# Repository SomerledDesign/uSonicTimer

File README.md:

# uSonicTimer

Firmware for a timer and heater controller I added to a cheap ultrasonic cleaner. It runs on an
**ESP8266 (ESP-12E module)**. A **Nokia 5110 (PCD8544, 84x48) LCD** shows a menu that you drive with a
**rotary encoder and its push button**. A **DS18B20 1-Wire temperature sensor** measures the bowl
temperature. Two outputs drive **solid-state relays** that switch the 110 VAC bowl **heater** and the
ultrasonic **cleaner**. The set temperature, timer preset, display unit (°F/°C), LCD contrast and
backlight brightness are saved in (emulated) EEPROM, so they survive a power cycle.

The menu approach comes from the [educ8s.tv](https://www.youtube.com/@Educ8s)
[menu tutorial](https://youtu.be/ak5TsUFhyf8?si=9JEMm8WbRyF4dVVC).

> Status: in active development (v0.6.1, PCB Rev D).

## What it does

1. On power-up it loads the settings from EEPROM. If a value is unset or out of range it uses a
   default: 72 °F, 10 min, °F, contrast 52 (raw 128), backlight level 10. It then initialises the
   LCD, the DS18B20, the encoder and the button.
2. It shows the main menu. You pick an item and a tap (short press) opens it; a long press toggles the backlight.
3. **Start** runs the cleaner for the set time and regulates the heater (the control logic always
   works in °F, with tenths; the screens show whole degrees in the chosen unit):
   - **Heating:** below set − 10 °F the **heater is ON**, the **cleaner is OFF** and the countdown
     **holds**. The screen shows the bowl temperature in big digits and "Heating to 120°F"; the
     rule under the digits fills as the bowl warms from where heating started to set − 8 °F.
   - **Cleaning:** at set − 8 °F or above (2 °F hysteresis) the **heater is OFF**, the **cleaner is
     ON** and the countdown runs. The screen shows the time left as big `MM:SS` with a blinking
     colon, the rule under it fills with the run's progress, and "Now 118 Set 120°F" underneath.
     If the bowl drops below set − 10 °F the heater comes back on and the countdown holds again.
     Only cleaning time counts towards the run.
   - **No sensor:** heater locked off, cleaner on, the countdown runs; the time screen shows
     "NO SENSOR" instead of the temperatures.
   - When the time is up both outputs switch off and a big **DONE** stays on screen until you turn
     or press; then the menu returns. A long press during the run aborts it (both outputs off).

## Menu tree

In the menus, rotating the encoder moves the reverse-video highlight (lists show 4 rows under the
title bar and scroll; small arrows mark more items). On the main menu a **short press** (tap) on
**Start** starts the timer and a tap on **Settings...** opens the Settings list; a **long press**
(> 1 s) on either toggles the LCD backlight between off and the level set in **Set backlight**.
In the Settings list a tap or a long press opens the highlighted item (**Exit** returns to the
main menu). The backlight is on at power-up.
Its state is kept while you are in a page, because presses inside the pages move the cursor
or confirm instead. After 5 minutes without input in the menu the backlight dims to about 20 %; the
first turn or press then only wakes it. Every button press is handled exactly once, so a press never
carries over into the next page.

**Encoder test:** hold the button while powering up (or pressing reset) to get a test screen with the
live A/B levels, the detent count and how often each input has changed; long press returns to the
menu. Both edge counts should rise together while turning. `ENCODER_STEPS_PER_DETENT` in
`src/main.cpp` is 2 for an encoder whose detents rest at both 00 and 11, 4 for one that always rests
at the same state.

The backlight also shows the status (it swings between the set brightness and about 30 % of it, so
the screen stays readable):

- **Steady**: normal operation (menu, cleaning).
- **Flashing** (1 Hz): heating up.
- **Pulsing** (slow): the timer has finished; stops at the next turn or press.
- **Double-blink** every 2 s: no temperature sensor during a run (heater locked off, cleaner runs).

Pulsing and double-blink also show when the backlight has been toggled off or set to level 0 (then
at level 5); heating and cleaning then stay dark.

```
Main menu "uSonicTimer"      (shows the set temperature and time underneath)
├── Start             heating screen (big temperature) / timer screen (big MM:SS) / DONE, as above
│                     long press = abort (both outputs off)
└── Settings...
    ├── Set temp      "ddd°F" (3 digits) or "dd°C" (2 digits), cursor digit in reverse video
    │                 rotate = change digit (0–9, wraps); press = next digit ("Press = next"),
    │                 press on the last digit = save and return ("Press = save");
    │                 long press = save from any digit (clamped 60–180 °F / 16–82 °C, stored in °F)
    ├── Set time      "<n> min"; rotate = preset 3, 8, 10, 15, 20, 30, 60 min (wraps)
    │                 press = save and return
    ├── Set units     "°F Fahrenheit" / "°C Celsius"; rotate = toggle, press = save and return
    ├── Set backlight "Off" / "Level 1"…"Level 10" with a bar; rotate = level (previewed live)
    │                 press = save, switch the backlight on and return
    ├── Set contrast  20–100 with a bar (mapped onto the usable raw 80–200); clockwise = higher,
    │                 accelerated (detents < 40 ms apart = 5 steps, < 90 ms = 2, else 1),
    │                 applied live; press = save and return
    └── Exit          back to the main menu
```

Settings are saved to EEPROM when you leave their page: set temperature `0x00` (°F), time `0x08`,
contrast `0x10` (raw 80–200, so the 0.5.0 value carries over), backlight level `0x18`, units `0x20`
(0 = °F, 1 = °C) and a layout id `0x28` (0x60) that marks EEPROM written by 0.6.0 or later. Every
value is range-checked on load; a backlight level of 0 is only accepted together with that id.

## Hardware (PCB rev 1d) pin map

The KiCad design files for this board are in [`hardware/uSonicTimer_1d/`](hardware/uSonicTimer_1d/).

| Signal | Arduino pin | ESP8266 GPIO | ESP-12E pin | Notes |
|---|---|---|---|---|
| LCD SCLK | D5 | GPIO14 | 5 | software SPI clock |
| LCD DIN | D7 | GPIO13 | 7 | software SPI data |
| LCD D/C | D10 | GPIO1 (TX) | 22 | shared with UART TX |
| LCD CS | D4 | GPIO2 | 17 | 10K pull-up |
| LCD RST | – | – | – | not connected (`U8X8_PIN_NONE`) |
| LCD backlight | D8 | GPIO15 | 16 | via Q1, 10K pull-down |
| Encoder CLK (A) | D0 | GPIO16 | 4 | 4K7 pull-up (R9), polled (no interrupt on GPIO16) |
| Encoder DT (B) | D6 | GPIO12 | 6 | 4K7 pull-up (R10), polled |
| Encoder SW | D9 | GPIO3 (RX) | 21 | shared with UART RX |
| Heater SSR | D2 | GPIO4 | 19 | HIGH = ON |
| Cleaner SSR | D1 | GPIO5 | 20 | HIGH = ON |
| DS18B20 1-Wire | D3 | GPIO0 | 18 | 4K7 pull-up; also ~PROGRAM strap |

On rev 1d, NPN transistors switch the heater and cleaner SSRs low-side. The logic is the same as
before: GPIO HIGH = ON.

The programming header is a set of 5 pogo pads: 1 GND, 2 RTS, 3 TX, 4 RX, 5 DTR. RTS and DTR
drive the auto-reset/boot circuit (Q2/Q3).

Because the UART pins are also used for the LCD D/C line and the encoder switch, serial output
from the `debug` build shares those lines with the hardware.

## Building and flashing (PlatformIO)

The project uses the `espressif8266` platform, board `esp12e` and the Arduino framework. It needs
these libraries, which PlatformIO fetches automatically from `platformio.ini`:
`olikraus/U8g2`, `lennarthennigs/ESP Rotary`, `lennarthennigs/Button2`, `paulstoffregen/OneWire`
and `milesburton/DallasTemperature`. `EEPROM` and `Ticker` come with the ESP8266 core.

```sh
pio run -e release                  # build the release firmware
pio run -e release -t upload        # flash it over the programming header
pio device monitor -b 115200        # serial monitor (debug output)
```

- `release` is the default environment (`default_envs = release`); it builds without the debug
  output.
- `debug` (`pio run -e debug`) adds `-Og -ggdb -g3 -D DEBUG -D WITH_GDB`. It enables the
  serial `debug()`/`debugln()` output at 115200 baud.
- `platformio.ini` puts `build_dir` and `libdeps_dir` under
  `$HOME/Library/Caches/PlatformIO/uSonicTimer/`, which keeps build output out of Dropbox. On a
  non-macOS machine, change these paths or remove them to use the default `.pio/` folder.

### Uploading over the pogo pins (FTDI 3.3 V cable, no DTR)

The programming cable (FTDI TTL-232R 3.3 V with LED) has no DTR line, so it can't put the ESP8266
into flash mode by itself. Do it by hand:

1. Short the sensor connector's data / 1-Wire line (GPIO0) to ground.
2. Turn the uSonicTimer on, or off and back on, so it boots into the bootloader. Power it from a
   5 V supply rather than mains, so no mains voltage is exposed on the bench.
3. Place the pogo pins on the programming pads: GND (black), RTS (green), the cable's TXD (orange) to
   the board's RX, and the cable's RXD (yellow) to the board's TX. Leave the cable's 5 V (red) and CTS (brown) unconnected.
4. Upload from VS Code (PlatformIO Upload). The upload speed is 115200.

Remove the GPIO0 short afterwards, then power-cycle the board to run the new firmware.

## Versioning

Firmware versions are a semantic version plus a build number, shown as **`0.6.2 (74)`** (current).

- Bump PATCH for fixes and MINOR for features; 1.0.0 is the first version installed and in service.
- The build number goes up by 1 for every build flashed for testing and never resets.
- `FW_VERSION`, `FW_BUILD` and `HW_REV` at the top of `src/main.cpp` set it. The startup screen
  shows `uSonicTimer` / `v0.6.2 (74)` / `PCB Rev D` for 1.5 s at power-up. Releases are tagged
  `vMAJOR.MINOR.PATCH` in git.

History:

- **0.6.2 (74)**: new button mapping. Main menu: tap on **Start** starts the timer, tap on
  **Settings...** opens the Settings list, long press on either toggles the backlight. Settings
  list: tap or long press opens the highlighted item.
- 0.6.1 (73): new big-digit font: blocky, squared-off 7-segment-style characters (4–5 px
  strokes, no diagonals, stepped slashed zero, colon of two 4x4 blocks) drawn from box lists in
  `include/bigfont.h`, closer to the reference clock than the scaled 5x7 font. Encoder
  acceleration in Set contrast (5 / 2 / 1 steps per detent for detents
  < 40 ms / < 90 ms / slower apart). A press saves in every settings page ("Press = save"); in Set
  temp a press moves to the next digit and saves on the last one, long press still saves anywhere.
  Detents still queued when a page closes no longer move the menu highlight.
- 0.6.0 (72): big-digit run screens in the style of a Nokia 5110 clock (Adafruit 5x7 digits
  scaled to 15x28 px, a rule that doubles as a progress bar, one line of small text): heating
  screen with the bowl temperature, timer screen with blinking colon, DONE screen. The countdown
  holds while heating (heater below set − 10 °F, cleaning resumes at set − 8 °F). Main menu is now
  Start / Settings...; Settings has Set temp, Set time, Set units (°F/°C, new), Set backlight
  (0 = off, new), Set contrast (shown as 20–100) and Exit, with title bars.
- 0.5.0 (71), `2d4bacc`: version defines, startup screen, versioning notes.
- Build 70, `a255348`: polled quadrature decoder (replaces ESPRotary) and the encoder test screen.
- Build 69, `44c0249`: backlight as status indicator and the Backlight brightness menu (`90cbc71`).

## Setup and usage

1. Wire the board as in the pin map, or use the rev 1d PCB. Put the DS18B20 on the bowl and
   connect the heater and cleaner through the SSRs.
2. Build and flash as above, then power up. The main menu appears.
3. Tap **Settings...** to open it and use **Set temp** to choose the target bowl temperature, **Set time**
   to choose the run time, **Set units** for °F or °C, and **Set backlight** / **Set contrast** for
   the LCD if needed. Each setting is saved when you leave its page.
4. Highlight **Start** and tap (short press). The display shows the bowl temperature while it heats, then
   the time left while it cleans; the heater and cleaner are controlled automatically.
5. Long-press at any time to stop. Both outputs switch off. When the time is up, DONE shows until
   you turn or press.

## Repository layout

- `src/main.cpp`: the firmware (setup, menus, pages, run control, EEPROM, backlight).
- `src/screens.cpp`, `include/screens.h`: drawing for the run screens, menus and settings pages.
- `include/ust_logic.h`: run-control hysteresis, °F/°C, contrast and progress helpers (no Arduino
  dependencies).
- `include/bigfont.h`: the big-digit font (blocky 15x28 characters as box lists, slashed zero).
- `tools/host/`: host-side test of `ust_logic.h` and a screen preview that runs the real drawing
  code against the U8g2 C library on a PC (`tools/host/build.sh`, writes PNGs to
  `tools/host/out/`).
- `src/sketch.md`: design notes and the original specification.
- `include/`: also the old splash/footer glyph bitmaps.
- `handoff.md`: latest status and decisions.
- `hardware/uSonicTimer_1d/`: KiCad project for the rev 1d controller board (schematic, PCB,
  project symbol/footprint libraries, Gerbers, interactive BOM and renders).
- `extras/` (git-ignored): local reference material. This includes third-party menu/encoder demo
  code, links to the KiCad hardware projects and links to the datasheets, which are archived
  centrally.

## License

uSonicTimer uses two licences, one for the code and one for the hardware:

- **Firmware and code** (`src/`, `include/`, `platformio.ini` and the rest of the software) are
  under the GNU General Public License, version 3 or later. See [`LICENSE`](LICENSE).
  SPDX-License-Identifier: GPL-3.0-or-later
- **Hardware design files** (everything under [`hardware/`](hardware/): the KiCad schematic,
  PCB, libraries and related fabrication files for the controller board, and the same files
  wherever else they are published for this project) are under the CERN Open Hardware Licence
  Version 2, Strongly Reciprocal. See [`LICENSE-HARDWARE`](LICENSE-HARDWARE).
  SPDX-License-Identifier: CERN-OHL-S-2.0

Both licences come with no warranty. This controller switches 110 VAC mains through solid-state
relays; build and use it at your own risk.

Copyright © 2024 Somerled Design, LLC.

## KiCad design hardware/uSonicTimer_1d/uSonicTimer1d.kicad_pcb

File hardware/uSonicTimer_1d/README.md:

# uSonicTimer controller board, rev 1d

KiCad 10 project for the uSonicTimer controller PCB (schematic rev D). The firmware
pin map in the top-level [`README`](../../README.md) matches this board.

| Path | Contents |
|---|---|
| `uSonicTimer1d.kicad_pro` | KiCad project (open this) |
| `uSonicTimer1d.kicad_sch` | Schematic |
| `uSonicTimer1d.kicad_pcb` | PCB layout |
| `uSonicTimer1d.kicad_dru` | Custom design rules |
| `uSonicTimer1d.kicad_sym`, `sym-lib-table` | Project symbol library |
| `uSonicTimer1d.pretty/`, `fp-lib-table` | Project footprint library |
| `3dmodels/` | Project 3D models folder (currently only a README: sources, licences and excluded models) |
| `Gerber/` | Fabrication outputs: Gerbers, drill files, job file and `uSonicTimer1d_revD_gerbers.zip` for ordering |
| `bom/ibom.html` | Interactive BOM (open in a browser) |
| `Renders/` | Top and bottom board renders |
| `[TODO]/` | Changes planned for the next board revision |

The library tables use `${KIPRJMOD}`, so the project opens from any location. Every
symbol and footprint is in the project libraries. Every 3D model comes from the stock
KiCad 10 3D library, so nothing is needed outside this folder and a standard KiCad 10
install. The encoder (ENC1) and the screw terminal (J1) have no 3D body: their
third-party models can't be redistributed. Sources and licences are listed in
[`3dmodels/README.md`](3dmodels/README.md).

Licensed under the CERN Open Hardware Licence Version 2, Strongly Reciprocal. See
[`LICENSE-HARDWARE`](../../LICENSE-HARDWARE).
SPDX-License-Identifier: CERN-OHL-S-2.0

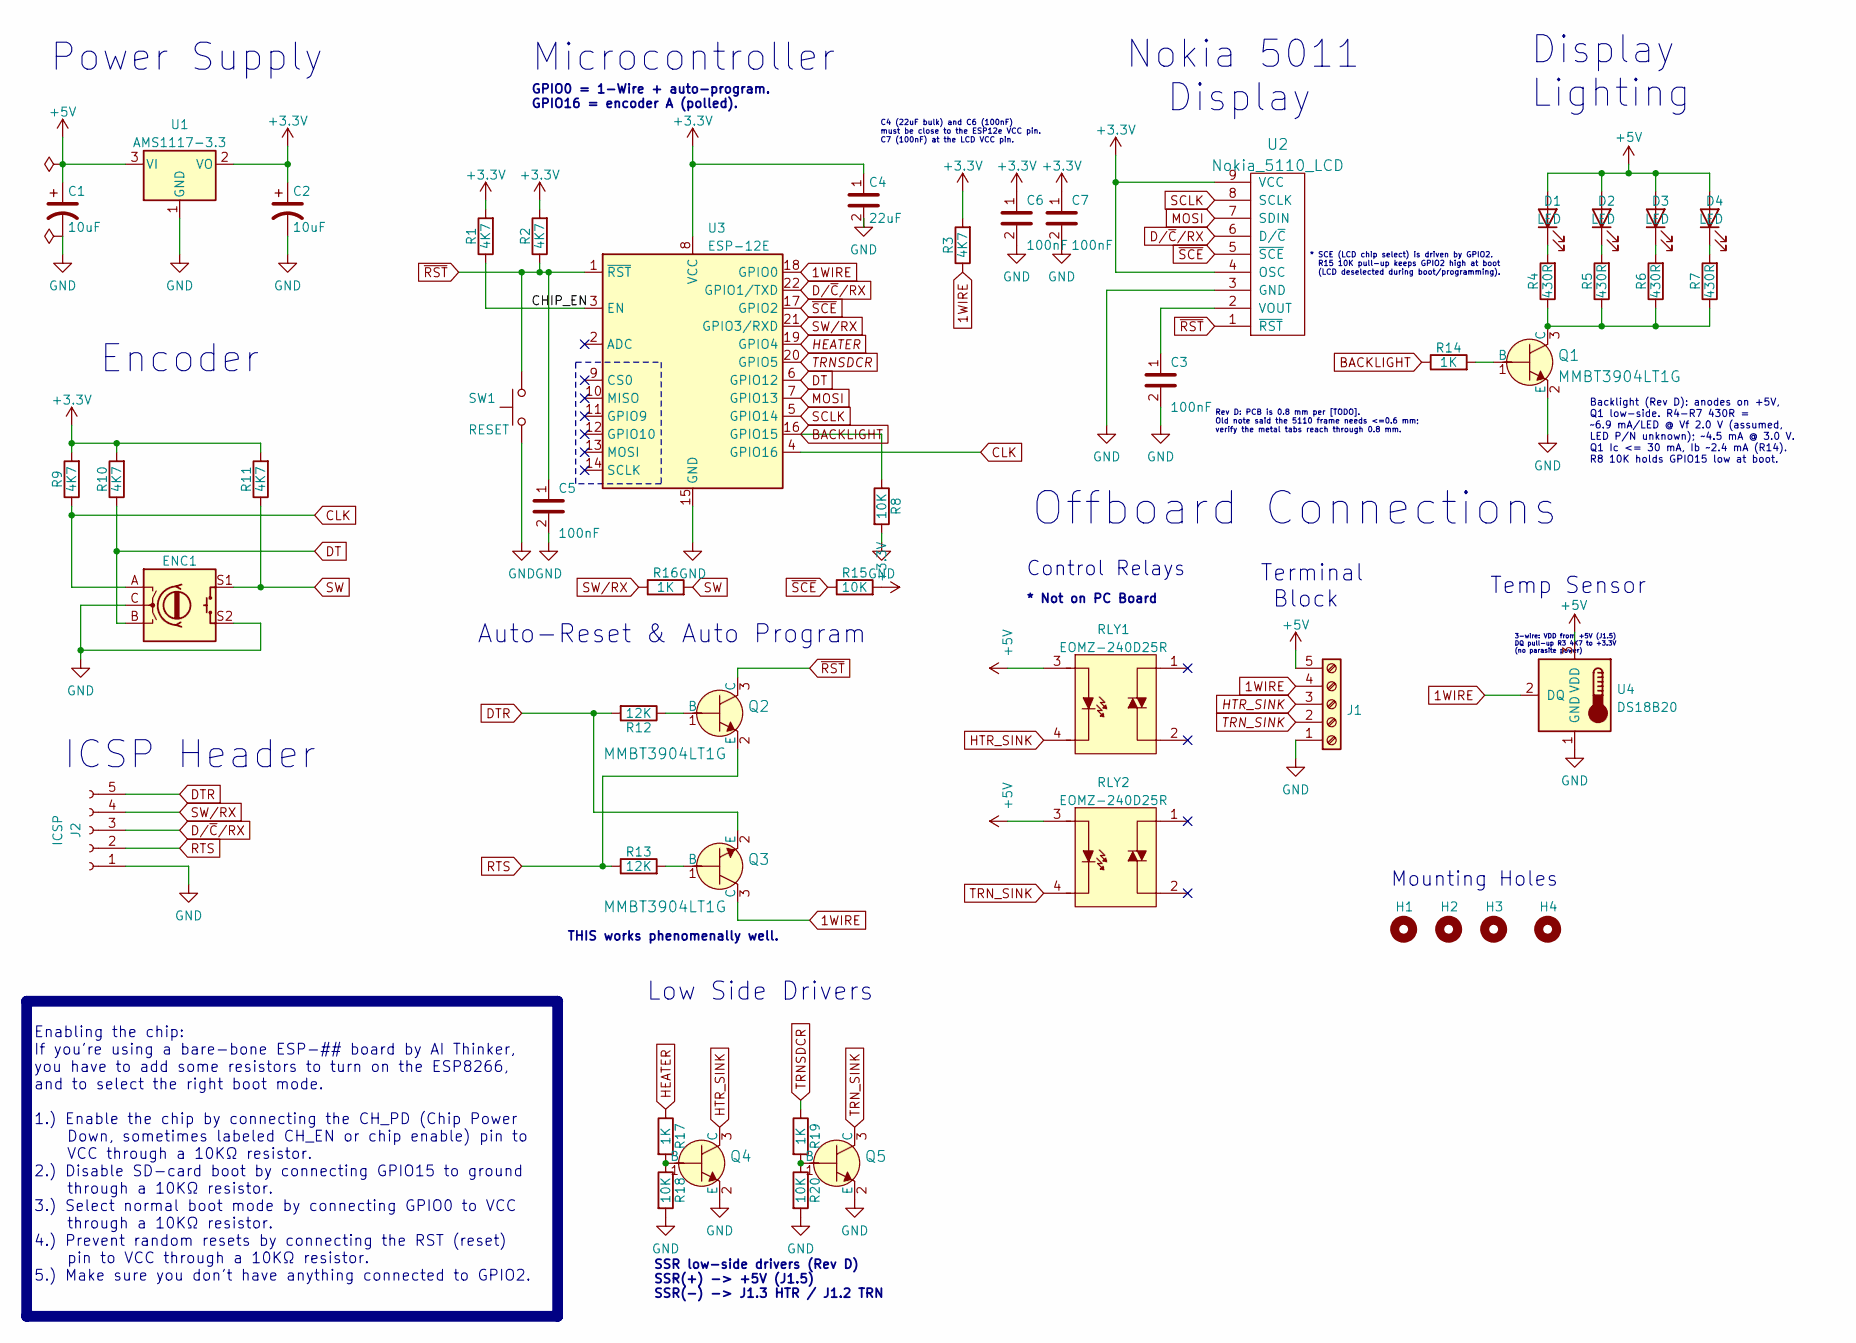
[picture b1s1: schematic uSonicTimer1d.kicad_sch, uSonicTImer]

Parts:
C1, C2: 10uF; CP_Elec_4x5.4; MPN UWT1C100MCL1GB; Digikey PN 493-2173-1-ND
C3, C5, C6, C7: 100nF; C_0805_2012Metric; MPN 08055C104KAT4A; Digikey PN 478-10836-1-ND
C4: 22uF; C_1206_3216Metric
D1, D3: LED; LED_0805_2012Metric
D2: LED; LED_0805_2012Metric_SilkTrim_D2
D4: LED; LED_0805_2012Metric_SilkTrim_D4
ENC1: RotaryEncoder_Switch; RotaryEncoder_Alps_EC11E-Switch_Vertical_H20mm
H1, H2, H3, H4: MountingHole; MountingHole_2.1mm
J1: Screw_Terminal_01x05; ScrewContact_ALLELEC_2,5_5-G-5,00_1x05_P5.00mm_Horizontal_c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
J2: ICSP; ICSP_5_POGO
Q1, Q2, Q3, Q4, Q5: MMBT3904LT1G; SOT-23-3; MPN MMBT3904LT1G; Digi-Key_PN MMBT3904LT1GOSCT-ND
R1, R2, R3, R9, R10, R11: 4K7; R_0805_2012Metric; MPN CRGCQ0805J4K7; Digikey PN A130138CT-ND
R4, R5, R6, R7: 430R; R_0805_2012Metric
R8, R15, R18, R20: 10K; R_0805_2012Metric; MPN CRGCQ0805J10K; Digikey PN A130140CT-ND
R12, R13: 12K; R_0805_2012Metric; MPN CRG0805F12K; Digikey PN A126337CT-ND
R14, R16, R17, R19: 1K; R_0805_2012Metric
RLY1, RLY2: EOMZ-240D25R; MPN EOMZ-240D25R; Digi-Key_PN SSR-240D25R
SW1: RESET; SW_Tactile_SPST_NO_Straight_CK_PTS636Sx25SMTRLFS
U1: AMS1117-3.3; SOT-223-3_TabPin2
U2: Nokia_5110_LCD; Nokia_5110-3310_LCD_uSonic1d
U3: ESP-12E
U4: DS18B20; TO-92_Inline

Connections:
1WIRE: J1.4, Q3.3 (C), R3.1, U3.18 (GPIO0), U4.2 (DQ)
+3.3V: C2.1, C4.1, C6.1, C7.1, R1.2, R2.2, R3.2, R9.2, R10.2, R11.2, R15.2, U1.2 (VO), U2.4 (OSC), U2.9 (VCC), U3.8 (VCC)
+5V: C1.1, D1.2 (A), D2.2 (A), D3.2 (A), D4.2 (A), J1.5, RLY1.3 (A), RLY2.3 (A), U1.3 (VI), U4.3 (VDD)
/CHIP_EN: R1.1, U3.3 (EN)
BACKLIGHT: R8.1, R14.1, U3.16 (GPIO15)
CLK: ENC1.A, R9.1, U3.4 (GPIO16)
DT: ENC1.B, R10.1, U3.6 (GPIO12)
DTR: J2.5, Q3.2 (E), R12.2
D/~C/RX: J2.3, U2.6 (D/~C), U3.22 (GPIO1/TXD)
GND: C1.2, C2.2, C3.2, C4.2, C5.2, C6.2, C7.2, ENC1.C, ENC1.S2, J1.1, J2.1, Q1.2 (E), Q4.2 (E), Q5.2 (E), R8.2, R18.2, R20.2, SW1.1, U1.1 (GND), U2.3 (GND), U3.15 (GND), U4.1 (GND)
HEATER: R17.1, U3.19 (GPIO4)
HTR_SINK: J1.3, Q4.3 (C), RLY1.4 (K)
MOSI: U2.7 (SDIN), U3.7 (GPIO13)
unnamed: D1.1 (K), R4.2
unnamed: D2.1 (K), R5.2
unnamed: D3.1 (K), R6.2
unnamed: D4.1 (K), R7.2
unnamed: Q1.1 (B), R14.2
unnamed: Q1.3 (C), R4.1, R5.1, R6.1, R7.1
unnamed: Q2.1 (B), R12.1
unnamed: Q3.1 (B), R13.2
unnamed: Q4.1 (B), R17.2, R18.1
unnamed: Q5.1 (B), R19.2, R20.1
unnamed: C3.1, U2.2 (VOUT)
RTS: J2.2, Q2.2 (E), R13.1
SCLK: U2.8 (SCLK), U3.5 (GPIO14)
SW: ENC1.S1, R11.1, R16.2
SW/RX: J2.4, R16.1, U3.21 (GPIO3/RXD)
TRNSDCR: R19.1, U3.20 (GPIO5)
TRN_SINK: J1.2, Q5.3 (C), RLY2.4 (K)
~RST: C5.1, Q2.3 (C), R2.1, SW1.2, U2.1 (~RST), U3.1 (~RST)
~SCE: R15.1, U2.5 (~SCE), U3.17 (GPIO2)

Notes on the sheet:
Auto-Reset & Auto Program
Terminal Block
SSR low-side drivers (Rev D) SSR(+) -> +5V (J1.5) SSR(-) -> J1.3 HTR / J1.2 TRN
Low Side Drivers
Control Relays
Mounting Holes
* SCE (LCD chip select) is driven by GPIO2. R15 10K pull-up keeps GPIO2 high at boot (LCD deselected during boot/programming).
Offboard Connections
Nokia 5011 Display
* Not on PC Board
GPIO0 = 1-Wire + auto-program. GPIO16 = encoder A (polled).
Microcontroller
Rev D: PCB is 0.8 mm per [TODO]. Old note said the 5110 frame needs <=0.6 mm; verify the metal tabs reach through 0.8 mm.
Display Lighting
ICSP Header
C4 (22uF bulk) and C6 (100nF) must be close to the ESP12e VCC pin. C7 (100nF) at the LCD VCC pin.
Temp Sensor
3-wire: VDD from +5V (J1.5) DQ pull-up R3 4K7 to +3.3V (no parasite power)
Power Supply
THIS works phenomenally well.
Encoder
Backlight (Rev D): anodes on +5V, Q1 low-side. R4-R7 430R = ~6.9 mA/LED @ Vf 2.0 V (assumed, LED P/N unknown); ~4.5 mA @ 3.0 V. Q1 Ic <= 30 mA, Ib ~2.4 mA (R14). R8 10K holds GPIO15 low at boot.
Enabling the chip: If you're using a bare-bone ESP-## board by AI Thinker, you have to add some resistors to turn on the ESP8266, and to select the right boot mode. 1.) Enable the chip by connecting the CH_PD (Chip Power Down, sometimes labeled CH_EN or chip enable) pin to VCC through a 10KΩ resist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

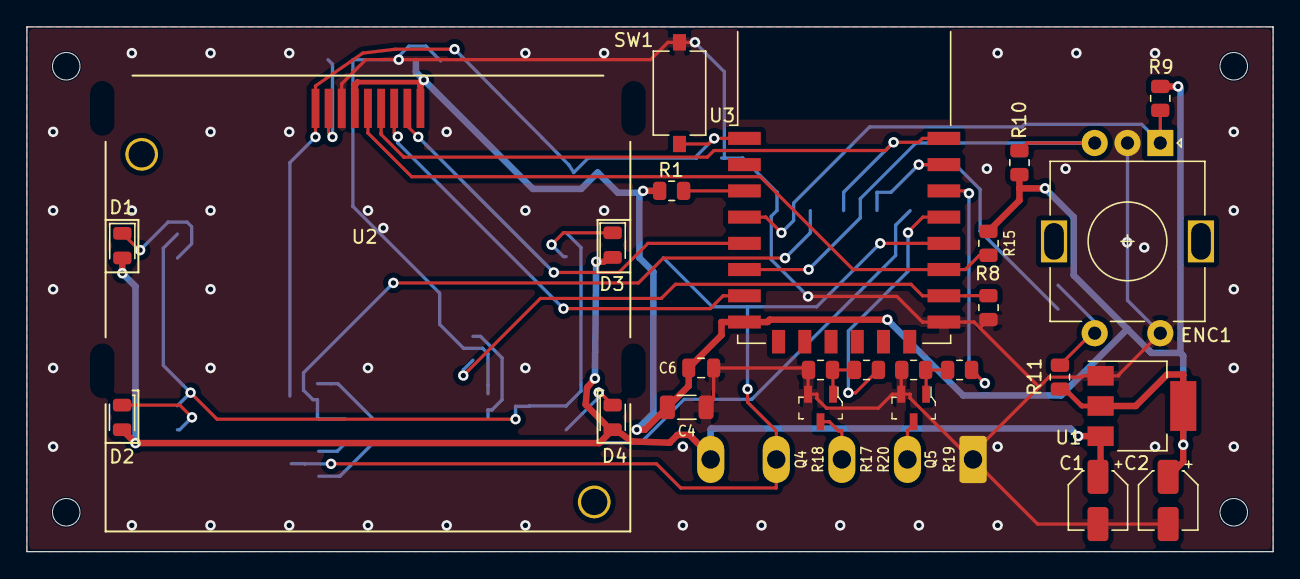
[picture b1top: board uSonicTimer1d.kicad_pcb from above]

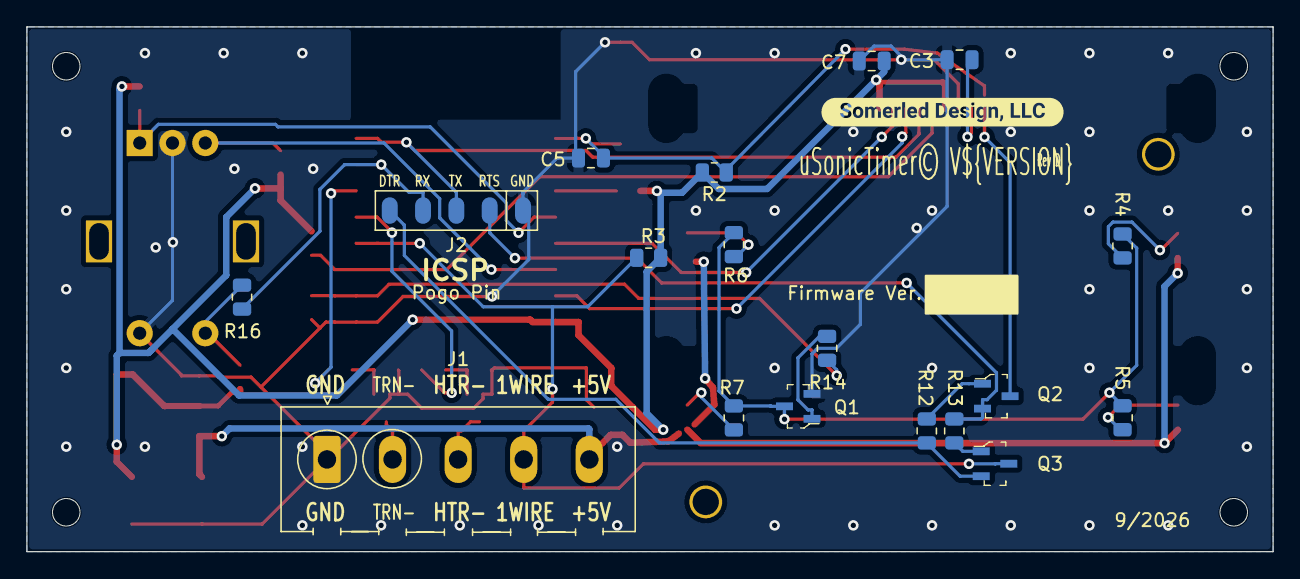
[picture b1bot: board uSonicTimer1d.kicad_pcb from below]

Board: 2 copper layers, 95.0 x 40.0 mm, 48 parts (19 on the bottom side), 32 nets.

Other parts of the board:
kibuzzard-63EC72D8: G***; kibuzzard-63EC72D8

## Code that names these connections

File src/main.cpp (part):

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/**
 *  Physical pins listed for comparison to pcb.
 *  in version 1b pcb 2/2023 the CS is connected to ground
 *  GPIO15 is used for
 *  PCB rev 1d (9/2026): LCD CS on GPIO2 (10K pull-up), backlight on GPIO15 (10K pull-down),
 *  1-Wire on GPIO0 (4K7 pull-up), encoder CLK on GPIO16. Heater/cleaner SSRs are now switched
 *  low-side by NPN transistors (GPIO HIGH = ON, same logic as before).
 *
 *
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 *   •   RST             1
 *
 *  --- Available  I/O ---
 *   •   GPIO0     D3   18
 *   •   GPIO1     D10  22  (TXD0) \
 *   •   GPIO3     D9   21  (RXD0)  |  If using as inputs don't call Serial.begin()
 *   •   GPIO2     D4   17  (TXD1)
 *
 *   •   GPIO4     D2   19  (SDA)   \
 *                                   }--> I2C
 *   •   GPIO5     D1   20  (SCL)   /
 *
 *   ◎   GPIO6     ☞    14  USED INTERNALLY - DO NOT USE **
 *   ◎   GPIO7     ☞    10  USED INTERNALLY - DO NOT USE **
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 *   ◎   GPIO10    ☞    12  USED INTERNALLY - DO NOT USE **
 *   ◎   GPIO11    ☞     9  USED INTERNALLY - DO NOT USE **
 *
 *   •   GPIO14    D5    5  (SCLK) | \ S
 *   ●   GPIO12    D6    6  (MISO) |  |  P
 *   •   GPIO13    D7    7  (MOSI) |  |    I
 *   •   GPIO15    D8   16  (CS)   | /      ..
 *   •   GPIO16    D0    4  (no interrupt)
 *   •   ADC0      A0    2  (Analog Input)
 *
 * ----------------------------------------------------------------------------------------
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 *      Func          Non i/o     Digitial     GPIO i/o     ESP12e Pin         Descr.                   Ω out
 *     =========================================================================================================
 *    1 RESET          RST        RST          -           1                  RESET line
 *    2 CS                        D4           GPIO2       17                 CHIP SELECT (10K pull-up)
 *    3 D/C                       D10/TX       GPIO1       22                 DATA|COMMAND
 *    4 DIN                       D7(MOSI)     GPIO13      7                  MOSI
 *    5 CLK                       D5(SCLK)     GPIO14      5                  SCLK
 *    6 VCC            3V
 *    7 BL                        D8           GPIO15      16                 Backlight (via Q1, 10K pull-down)
 *    8 GND
 *
 *    Rotary Encoder
 *      Func          Non i/o     Digitial     GPIO i/o     ESP12e Pin        Descr.         Ω out
 *     ===========================================================================================
 *      ROT_ENC_A_PIN             D0           GPIO16      4                  CLK (4K7 pull-up, R9) ✓
 *      ROT_ENC_B_PIN             D6           GPIO12      6                  DT (4K7 pull-up, R10) ✓
 *      ROT_ENC_BUTTON_PIN        D9           GPIO3       21                 SW(/RX)           ✓
 *
 *    Relays
 *      Func          Non i/o     Digitial     GPIO i/o     ESP12e Pin         Descr.
 *     =====================================================================================
 *      HEATER_ENABLE_PIN         D2           GPIO4       19                 Heater relay
 *      DEVICE_ENABLE_PIN         D1           GPIO5       20                 Cleaner relay
 *
 *    Dallas Temp Sensor (DS18B20)
 *      Func          Non i/o     Digitial     GPIO i/o     ESP12e Pin         Descr.
 *     =====================================================================================
 *      ONE_WIRE_BUS              D3           GPIO0       18                  4K7 pull-up; also ~PROGRAM
 *
 *    ICSP Header (5 pin pogo pads)
 *      Func             Header pin    to -->                       ESP12e Pin    Ω out
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#endif // DEBUG

// Pin definitions (PCB rev 1d)
#define ONE_WIRE_BUS D3 // GPIO0 (4K7 pull-up, shared with ~PROGRAM)

#define CLEANER_PIN D1  // GPIO5
#define HEATER_PIN D2   // GPIO4

#define ROTARY_PIN1 D0     // GPIO16, CLK (polled; no interrupt on GPIO16)
#define ROTARY_PIN2 D6     // GPIO12, DT
#define ROTARY_BUTTON D9   // GPIO3, SW/RX

#define BACKLIGHT_PIN D8 // GPIO15 (10K pull-down, drives Q1)

#define LCD_SCLK_PIN D5   // GPIO14
#define LCD_DIN_PIN D7    // GPIO13
#define LCD_DC_PIN D10    // GPIO1 (TX)
#define LCD_CS_PIN D4      // GPIO2 (10K pull-up)
#define LCD_RST_PIN U8X8_PIN_NONE
// Status LED
// The backlight (PWM on GPIO15) is used as the status indicator, see updateBacklight():
// Steady       = normal operation (menu idle, cleaning) at the Set backlight level
// Flashing     = Heating up (1 Hz between the set brightness and ~30% of it)
// Pulsing      = timer finished, until any input (shows even if the backlight is toggled off)
// Double-blink = no temp sensor during a run, heater locked off (shows even if toggled off)
// Dim          = ~20% after 5 minutes idle in the menu; the first input only wakes it
// Heating/cleaning stay dark when the backlight has been toggled off or set to level 0.
// #define STATUS_LED_PIN ?   (not needed: the backlight is the status LED)
// bool statusLedOn = false;

// Encoder transitions per detent: 2 = half-cycle encoder (detents rest at both 00 and 11),
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uint16_t longPress = 1000;   // one second long press of button
bool g_backlightOn = true;   // backlight state; toggled by a long press in the main menu
uint8_t g_backlightLevel;    // backlight brightness level 0..10 (0 = off; Set backlight page)
uint8_t g_previewLevel = 0;  // level previewed while the Set backlight page is open
bool g_previewActive = false; // true while the Set backlight page previews g_previewLevel

// EEPROM layout (one byte per setting; addresses kept from earlier firmware so saved
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#define EEPROM_ADDR_BACKLIGHT 0x18 // uint8_t g_backlightLevel
#define EEPROM_ADDR_UNITS     0x20 // uint8_t UNITS_F / UNITS_C (new in 0.6.0)
#define EEPROM_ADDR_LAYOUT    0x28 // uint8_t EEPROM_LAYOUT_ID, written by 0.6.0 and later
#define EEPROM_LAYOUT_ID      0x60 // marks a layout that knows backlight level 0 and the units byte
#define UNITS_F               0
#define UNITS_C               1
static_assert(EEPROM_ADDR_SET_TEMP + sizeof(uint8_t) <= EEPROM_ADDR_TIMER, "EEPROM: set temp overlaps timer");
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
    // Initialize rotary encoder (polled by pollEncoder() from loop context)
    ///////////////////////////////////////////////////////////////
    // GPIO16 has no internal pull-up (R9 4K7 is external) and the core's pinMode(16, INPUT_PULLUP)
    // leaves the GPIO16 output enable untouched; INPUT explicitly makes it an input
    pinMode(ROTARY_PIN1, INPUT);
    pinMode(ROTARY_PIN2, INPUT_PULLUP); // R10 4K7 external as well
    g_encState = (digitalRead(ROTARY_PIN1) << 1) | digitalRead(ROTARY_PIN2);
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    // Initialize pins
    ///////////////////////////////////////////////////////////////

    pinMode(BACKLIGHT_PIN, OUTPUT); // GPIO15 is held LOW by its pull-down until here (boot strap)
    analogWriteRange(255);
    analogWriteFreq(BACKLIGHT_PWM_FREQ);
    turnOnBacklight(); // backlight starts on at the saved level; a long press in the main menu toggles it
    g_lastActivityMs = millis();
    pinMode(HEATER_PIN, OUTPUT);
    pinMode(CLEANER_PIN, OUTPUT);
    digitalWrite(HEATER_PIN, LOW);
    digitalWrite(CLEANER_PIN, LOW);

    // startup screen (name, version, board revision) for STARTUP_SCREEN_MS
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/**
 * @brief Quadrature decoder for the rotary encoder (replaces ESPRotary).
 *
 * Reads A (GPIO16) and B (GPIO12) directly and counts Gray-code transitions. Detents are
 * only counted in a rest state (A == B), so contact bounce cancels out and the count lines
 * up with the detents by itself. A sample that skipped the middle state (both pins changed)
 * counts as two steps in the direction of the last valid one. Never yields; call it often.
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/**
 * @brief Encoder test screen: hold the encoder button during power-up/reset to get here.
 *
 * Shows the live A (GPIO16) and B (GPIO12) levels, the detent count and how often each input
 * has changed. Turning should make both edge counts rise together. An edge count that stays
 * at 0 means that input never reaches the ESP8266 (check the module pad/trace), not firmware.
 * Resting levels that alternate 00/11 between detents mean ENCODER_STEPS_PER_DETENT 2.
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/**
 * @brief Turns on the heater
 *
 * This function will turn on the heater by setting the HEATER_PIN
 * high and setting the heaterOn flag to true.
 */
void turnOnHeater()
{
    // Turn on the heater
    digitalWrite(HEATER_PIN, HIGH);
    heaterOn = true;
}
/**
 * @brief Turns off the heater
 *
 * This function will turn off the heater by setting the HEATER_PIN
 * low and setting the heaterOn flag to false.
 */
void turnOffHeater()
{
    // Turn off the heater
    digitalWrite(HEATER_PIN, LOW);
    heaterOn = false;
}

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/**
 * @brief Writes the backlight PWM duty (0-255), only when it changes.
 *
 * All backlight writes go through here: a digitalWrite() on the pin would stop the PWM.
 */
void setBacklightDuty(uint8_t duty)
{
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        return;
    }
    lastDuty = duty;
    analogWrite(BACKLIGHT_PIN, duty);
}

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
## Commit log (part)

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2022-01-16 alright, don't get too excited just the splash is working...
2022-01-30 switched to U8G2 library from AdafruitGFX
2024-08-30 rewrite by GROK2.mini
2024-10-01 added RoughTime.h and cleaned up Grok code
2026-01-03 finished commit. wait on hardware
2026-01-19 added agents.md, handoff.md
2026-03-20 WIP: long-press submenu entry, cursor-based Contrast; spec/handoff notes; monitor_port commented

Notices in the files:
src/main.cpp:
@copyright Copyright (c) 2024 Somerled Design, LLC in Kevin Murphy
This program is free software : you can redistribute it and/or modify
it under the terms of the GNU General Public License as published by
the Free Software Foundation, either version 3 of the License, or
(at your option) any later version.
